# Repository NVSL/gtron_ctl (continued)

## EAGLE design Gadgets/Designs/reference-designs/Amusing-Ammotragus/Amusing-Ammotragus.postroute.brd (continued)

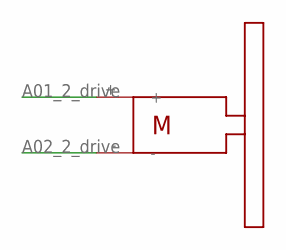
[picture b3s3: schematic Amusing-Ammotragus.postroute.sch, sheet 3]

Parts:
U3: SOLARBOTICS_GM2; SOLARBOTICS_G2

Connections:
A01_2_DRIVE: U3.+; also elsewhere on the board
A02_2_DRIVE: U3.-; also elsewhere on the board

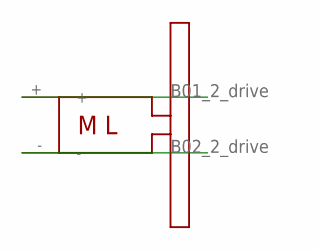
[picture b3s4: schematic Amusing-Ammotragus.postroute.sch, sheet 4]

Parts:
U5: SOLARBOTICS_GM2_LEFT; SOLARBOTICS_G2_LEFT

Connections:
B01_2_DRIVE: U5.+; also elsewhere on the board
B02_2_DRIVE: U5.-; also elsewhere on the board

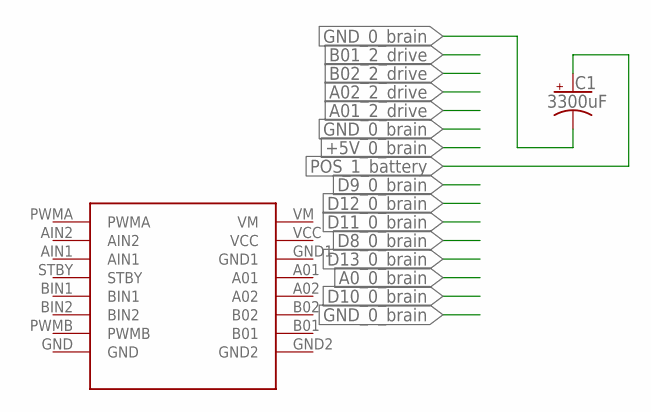
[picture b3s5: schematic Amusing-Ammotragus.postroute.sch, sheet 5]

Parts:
C1: 3300uF; CAPPRD750W80D1600H2200P; MPN ECA-1EM332
U2: SPARKFUN_DUAL_MOTOR_DRIVER-BOB; SPARKFUN_DUAL_MOTOR_DRIVER

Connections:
+5V_0_BRAIN: U2.VCC; also elsewhere on the board
A0_0_BRAIN: U2.BIN2; also elsewhere on the board
A01_2_DRIVE: U2.A01; also elsewhere on the board
A02_2_DRIVE: U2.A02; also elsewhere on the board
B01_2_DRIVE: U2.B01; also elsewhere on the board
B02_2_DRIVE: U2.B02; also elsewhere on the board
D8_0_BRAIN: U2.STBY; also elsewhere on the board
D9_0_BRAIN: U2.PWMA; also elsewhere on the board
D10_0_BRAIN: U2.PWMB; also elsewhere on the board
D11_0_BRAIN: U2.AIN1; also elsewhere on the board
D12_0_BRAIN: U2.AIN2; also elsewhere on the board
D13_0_BRAIN: U2.BIN1; also elsewhere on the board
GND_0_BRAIN: C1.2 (-), U2.GND, U2.GND1, U2.GND2; also elsewhere on the board
POS_1_BATTERY: C1.1 (+), U2.VM; also elsewhere on the board

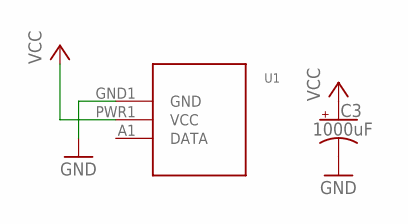
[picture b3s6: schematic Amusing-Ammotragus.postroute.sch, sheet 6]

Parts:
C3: 1000uF; CAPPRD500W80D1000H2200P; MPN ECA-1EM102
U1: MICRO_GRIPPER

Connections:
D3_0_BRAIN: U1.A1 (DATA); also elsewhere on the board
GND_0_BRAIN: C3.2 (-), U1.GND1 (GND); also elsewhere on the board
POS_1_BATTERY: C3.1 (+), U1.PWR1 (VCC); also elsewhere on the board

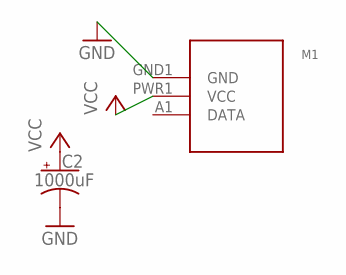
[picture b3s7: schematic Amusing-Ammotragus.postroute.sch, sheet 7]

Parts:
C2: 1000uF; CAPPRD500W80D1000H2200P; MPN ECA-1EM102
M1: SERVO-MICRO_SIDE_GLUE; SERVO_MICRO_SIDE_GLUE

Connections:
D4_0_BRAIN: M1.A1 (DATA); also elsewhere on the board
GND_0_BRAIN: C2.2 (-), M1.GND1 (GND); also elsewhere on the board
POS_1_BATTERY: C2.1 (+), M1.PWR1 (VCC); also elsewhere on the board

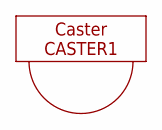
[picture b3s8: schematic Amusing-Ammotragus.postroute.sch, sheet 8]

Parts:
CASTER1: CASTERADAFRUIT-3/4IN; ADAFRUIT-3/4IN-CASTER

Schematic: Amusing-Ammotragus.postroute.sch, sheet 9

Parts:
J3: HEADER-0.1IN-2POS-FEMALE; HDRV2W63P254_2X1_508X254H838_HS

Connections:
D10_0_BRAIN: J3.2; also elsewhere on the board
GND_0_BRAIN: J3.1; also elsewhere on the board

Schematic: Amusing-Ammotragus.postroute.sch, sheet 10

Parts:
J2: HEADER-0.1IN-4POS-FEMALE; HDRV4W63P254_4X1_1016X254H838_HS

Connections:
+5V_0_BRAIN: J2.4; also elsewhere on the board
A4_0_BRAIN: J2.3; also elsewhere on the board
A5_0_BRAIN: J2.2; also elsewhere on the board
GND_0_BRAIN: J2.1; also elsewhere on the board

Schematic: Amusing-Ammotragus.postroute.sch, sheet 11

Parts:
J1: HEADER-0.1IN-4POS-FEMALE; HDRV4W63P254_4X1_1016X254H838_HS

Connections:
+5V_0_BRAIN: J1.4; also elsewhere on the board
GND_0_BRAIN: J1.1; also elsewhere on the board
RXD1_0_BRAIN: J1.3; also elsewhere on the board
TXD1_0_BRAIN: J1.2; also elsewhere on the board

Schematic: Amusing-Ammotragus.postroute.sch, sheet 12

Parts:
J4: HEADER-0.1IN-3POS-MALE; HDRV3W63P254_3X1_762X254H838_HS

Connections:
D5_0_BRAIN: J4.2; also elsewhere on the board
GND_0_BRAIN: J4.1; also elsewhere on the board
POS_1_BATTERY: J4.3; also elsewhere on the board

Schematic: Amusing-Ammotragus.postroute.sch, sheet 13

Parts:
C4: 1000uF; CAPPRD500W80D1000H2200P; MPN ECA-1EM102
U6: MICRO_GRIPPER

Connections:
D6_0_BRAIN: U6.A1 (DATA); also elsewhere on the board
GND_0_BRAIN: C4.2 (-), U6.GND1 (GND); also elsewhere on the board
POS_1_BATTERY: C4.1 (+), U6.PWR1 (VCC); also elsewhere on the board

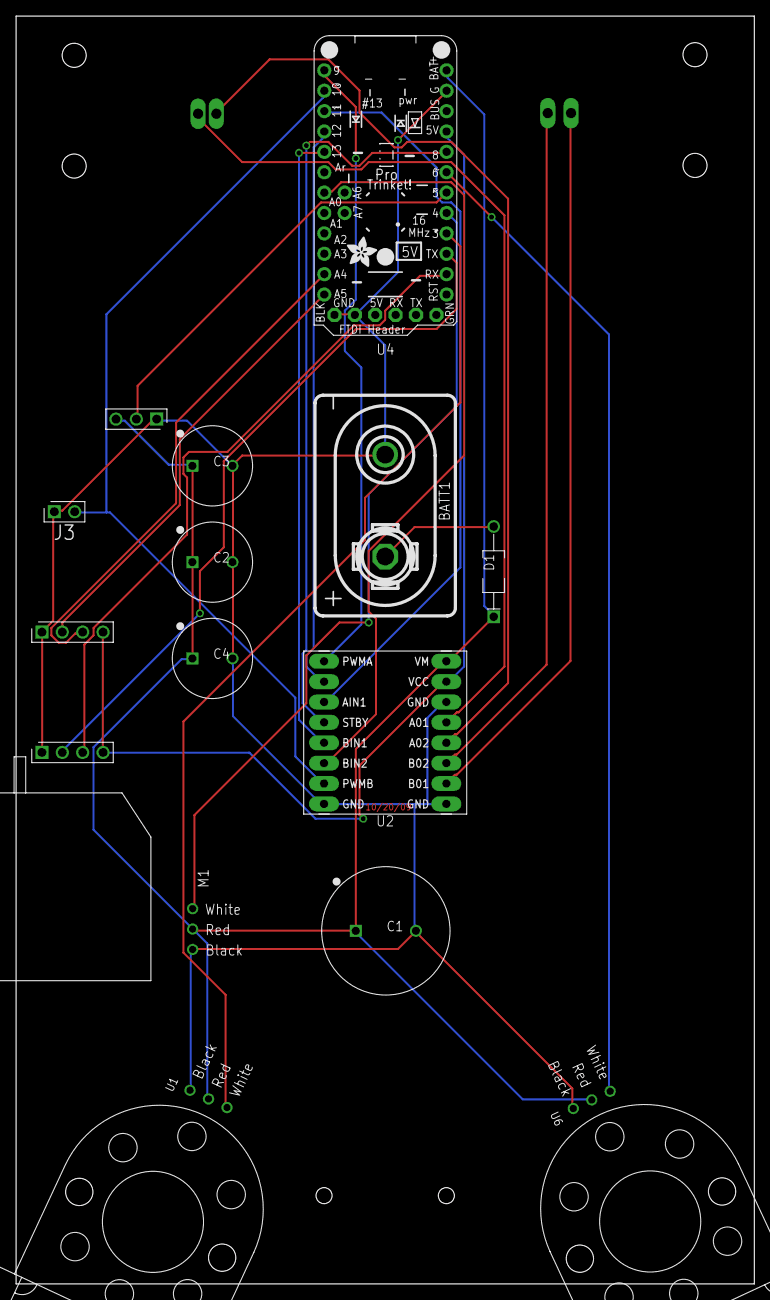
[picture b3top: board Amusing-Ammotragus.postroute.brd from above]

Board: 2 copper layers, 92.0 x 158.0 mm, 19 parts (1 on the bottom side), 23 nets.

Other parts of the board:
LOGO: BUILT_WITH_GADGETRON

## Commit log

2015-10-02 moved
2015-10-02 renaming
2015-10-02 tweaks
2015-10-02 revised setup
2015-10-02 bake in my username
2015-10-03 Refactor; move env in here; fix perms
2015-10-03 fix perms
2015-10-03 massive refactor
2015-10-03 mv venv
2015-10-04 update for new scripts
2015-10-04 anonymous git
2015-10-04 node packages
2015-10-04 better log management
2015-10-04 create log dir
2015-10-04 missing source include
2015-10-04 syntax error
2015-10-04 create ssh key correctl
2015-10-04 get username
2015-10-04 get ssh key correctly
2015-10-05 cleanup
2015-10-05 fix install checks
2015-10-05 Factor out everything possible from get_gadgetron because github raw retrieval is flaky
2015-10-05 Set up env right
2015-10-05 source the right files
2015-10-05 Call scripts correctly
2015-10-05 activate
2015-10-05 Fixes
2015-10-07 set USE_VENV for compatibility with svn trunk
2015-10-08 Add support for other users.
2015-10-08 support other users.
2015-10-08 Uses the SVN trunk
2015-10-08 Manage username correctly
2015-10-12 Gadgetron workspace management system. First draft.
2015-10-15 Sanity checking. Working directory handling. Fixups for legacy scripts to work wit gtron
2015-10-16 Editing the config file. Delaying variable evaluation. Utility commands (config_set, config_unset, add_repo, remove_repo, config_dump).
2015-10-16 Gtron-ized setup/update scripts
2015-10-17 fix variable expansion
2015-10-17 Selective directory operations and factored out iterating over directories. Improved directory handling. Better information hiding in Workspace object.
2015-10-18 Better directory handling. Control over processing order of repos
2015-10-19 Don't create log if you are doing a dry run
2015-10-20 Improved code formatting. Use logging module
2015-10-20 added variable for svn branch
2015-10-22 Improved exception reporting. Improved variable evaluation.
2015-10-24 added new_design. Support for git username. Support for supressing build in some directories
2015-10-24 Fix logging for dry runs. Fix silly error in Workspace constructor
2015-10-24 Support for local config
2015-10-26 Fix typo
2015-10-26 make setup_gadgetron work before everything is setup
2015-10-26 fixed stupid shell OR syntax
2015-10-26 write out no build
2015-10-26 use uppercase instead of upper
2015-10-26 use upper instead of uppercase
2015-10-29 Added test target
2015-10-30 factor out directory command reporting
2015-11-06 update full_install script and related changes.
2015-11-06 Make it run without any support files
2015-11-06 Fixed typo
2015-11-06 Added note to ignore spurious warnings.
2015-11-06 Initial documentation of gtron
2015-11-06 prepare for sphinx docs
2015-11-06 Some documentation.
2015-11-06 Removed outdated targets
2015-11-06 Documentation for gtron commands
2015-11-06 Command to build and display docs
2015-11-06 don't forget to import
2015-11-06 Bug reporting instructions
2015-11-07 Bug reporting in docs. test command. ubt command
2015-11-07 Describe other config files
2015-11-07 Don't require github to work until we've set it up
2015-11-07 Make SSH key setup work (maybe)
2015-11-07 fix NVSL user login
2015-11-07 python packages for cbc
2015-11-07 Complete set of repos for gadgetron
2015-11-07 Updates for git migration
2015-11-07 bug fixes
2015-11-07 checkout develop branch by default
2015-11-08 Option to choose a branch on update
2015-11-08 Push ssh keys with curl
2015-11-08 Fix typos. Always push ssh key to github
2015-11-08 Fix typos. Messages about pushing ssh keys
2015-11-08 use the right branch
2015-11-08 include gcam in pythonpath
2015-11-08 better messages. Correct log file name
2015-11-08 better messages
2015-11-08 Don't need a Makefile anymore
2015-11-08 make it easy to change the branch we are working on.
2015-11-08 automatically checkout new designs
2015-11-08 Better name for github key
2015-11-11 Fix build order
2015-11-11 Make 'master' the default branch. Better support for branching on 'update'
2015-11-11 Use master branch.
2015-11-11 User the nvsl user
2015-11-11 fix initial checkout
2015-11-11 Fix build order for CBC
2015-11-11 choose branch wisely
2015-11-11 Ensure ssh key exists
2015-11-11 turn off nvsl user
2015-11-11 turn off more bb cluster stuff
2015-11-11 Sort by int ordering, not string ordering. Collect output of sub processes
2015-11-12 handle missing directories more gracefully
2015-11-12 add ubt command line options. --force gives no errors
2015-11-12 Reorder for easier use
2015-11-12 Automate ssh key gen
2015-11-12 cleanup node install output
2015-11-12 cleanup fixup output
2015-11-12 better sshkey-gen automation
2015-11-12 clean up progress messages
2015-11-12 Clean up output more
2015-11-12 record fewer logs
2015-11-12 provide more timely output
2015-11-12 Pretty failures w/ tail of command output
2015-11-13 Changed suffix on log files to '.txt'
2015-11-13 Move install logs to 'gtron-log.txt'
2015-11-14 Ensure apt-get is up-to-date
2015-11-14 Log apt-get update
2015-11-14 Make sure we have git and curl
2015-11-14 Check for command failure and exit on failure
2015-11-14 Error checking
2015-11-14 remove unnecessary checks
2015-11-14 Add BOMGenerator
2015-11-14 update self on 'gtron update'. close issue #8
2015-11-15 More flexible do_cmd() to capture stderr on command failure. Handle missing upstream branch on gtron update.
2015-11-15 Fail without brew
2015-11-15 Fail without brew; collect logs and verify success
2015-11-16 better logging. Build Swoop first. Find eagle after install
2015-11-16 Automatically detect completion of eagle installer
2015-11-16 Automatically detect completion of GAE installation
2015-11-16 Wait for GAE install copy to complete.
2015-11-16 Do the GAE copy ourselves
2015-11-16 Create ~/eagle to make Eagle happy
2015-11-16 Terminate early for setting up testing parts of the build
2015-11-17 don't instal gae and eagle, if they are already there
2015-11-19 rpiutil path in gtron_env
2015-11-19 Revert "Merge branch 'master' of github.com:NVSL/gtron_devel"
    This reverts commit 8fb9ca6676ab2733c32c2e6f5864ef664dd2a4db, reversing
    changes made to a495ee8c5c7792b4e3b21f5732fb4b551cb003b1.
2015-11-25 Keep newline at end of config file
2015-11-26 install grunt-npm-install globally
2015-11-26 Make ubt work properly
2015-11-26 Revert "Revert "Merge branch 'master' of github.com:NVSL/gtron_devel""
    This reverts commit 422ad5f8452e07ecfc7b692b1a0c41f0280c8fcf.
2015-11-26 remove hasattr
2015-12-14 Added EagleServer
2015-12-19 add zip to ubuntu packages to install. GAE needs it. reslolves #11
2015-12-31 EagleServer goes in Gadgets/Tools not in the root of the repo.
2015-12-31 Add prerequisites for Shapely
2016-01-15 Add matplotlib, this should fix #14
2016-02-04 add webapp2 to local python packages
2016-02-11 Added TAZI to workspace.json
2016-02-24 Added GadgetMaker2 to PYTHONPATH
2016-02-25 small fixes
2016-02-26 added webob for webapp2 in EagleServer
2016-02-26 added descartes for Shapely
2016-03-02 install local python. Re-order repos
2016-03-02 gtron push command
2016-03-04 actually use the ubuntu_packages.txt file
2016-03-04 install the right geos lib
2016-03-29 avoid spurious apt-get failures. Fix deps for matplotlib
2016-04-13 actually use brewconfig
2016-04-14 disable gsutil. Seems to have disappeared from pypi
2016-04-14 re-enalbed gsutil. Not actually broken
2016-05-11 added server eagle support
2016-05-11 fixed gcloud eagle path
2016-07-05 error checking on download
2016-07-11 grunt-npm-install@0.3.0 wants grunt@~0.4.1
2016-07-14 added doxygen to package list
2016-07-18 Added PubSubWrapper to workspace
2016-07-18 added PubSubWrapper to gtron
2016-07-20 added geocheck to workspace
2016-07-20 added 7.6.0 and disabled eagle server eagle search
2016-07-21 added apiclient
2016-07-21 update python packages (and pip)
2016-07-21 add setup tools
2016-07-21 install packages one at a time
2016-07-24 gtron can now update on large pathnames, added forked adafruit repos
2016-07-26 create venv before installing in it
2016-07-26 Order installation correctly.
2016-07-27 reorder workspace
2016-07-31 new command for checking repo status. get rid of svn support
2016-08-02 removed grunt-npm-install
2016-08-03 better test for if the venv is set up
2016-08-04 auto auth git clone
2016-08-04 changed over to https for checkout
2016-08-04 changed over to ssh for checkout
2016-08-04 back to normal git clone
2016-08-08 update didn't raise on mkdir error
2016-08-08 mkdir error reporting on update
2016-08-08 better logging and seperated some update cmds
2016-08-08 getcwd in os not os.path
2016-08-08 added to git checkout too
2016-08-08 do_cmd("cd") wasn't working so I changed to os.chdir
2016-08-08 added no build to server tool dirs
2016-08-08 raise error in chdir to critical but removed exit(-1)
2016-08-10 Tweaks and adjustments for everything being a module
2016-08-15 reorg workspace order to respect dependencies
2016-08-15 new env script for setupified build
2016-08-15 new option to get list of repos. better error reporting.
2016-08-17 added 'release', 'bump_version', and improved 'cmd'
2016-08-17 added gcloud
2016-08-17 typo
2016-08-22 added server scripts to workspace. Various imprements in flexibility
2016-08-31 allow gtron_devel to be a workspace repo; and allow for parallel operation with --parallel
2016-08-31 utility functions/features
2016-08-31 pycharm stuff
2016-08-31 pycharm stuff; use correct paths
2016-08-31 bug fix
2016-09-01 Remove pycharm stuff
2016-09-01 gitignore
2016-09-01 version
2016-09-01 Set version
2016-09-02 fix gtron.py
2016-09-02 fix makefile
2016-09-02 new version
2016-09-02 Pull release as needed during gtron release. Resolves #20
2016-09-02 don't die because of log problems
2016-09-16 reference designs
2016-09-17 add reference design repo
2016-09-18 new 'git' command
2016-09-21 use gtron.py
2016-09-21 include webob
2016-09-22 Added FAILED message to gtron update if pulling a repo fails
2016-10-29 Added double in echo quotes to prevent a error
2016-11-01 add quetzal
2016-11-01 quoting fix
